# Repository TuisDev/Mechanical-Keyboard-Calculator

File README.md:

# Mechanical-Keyboard-Calculator
A scientific calculator that has mechanical keys

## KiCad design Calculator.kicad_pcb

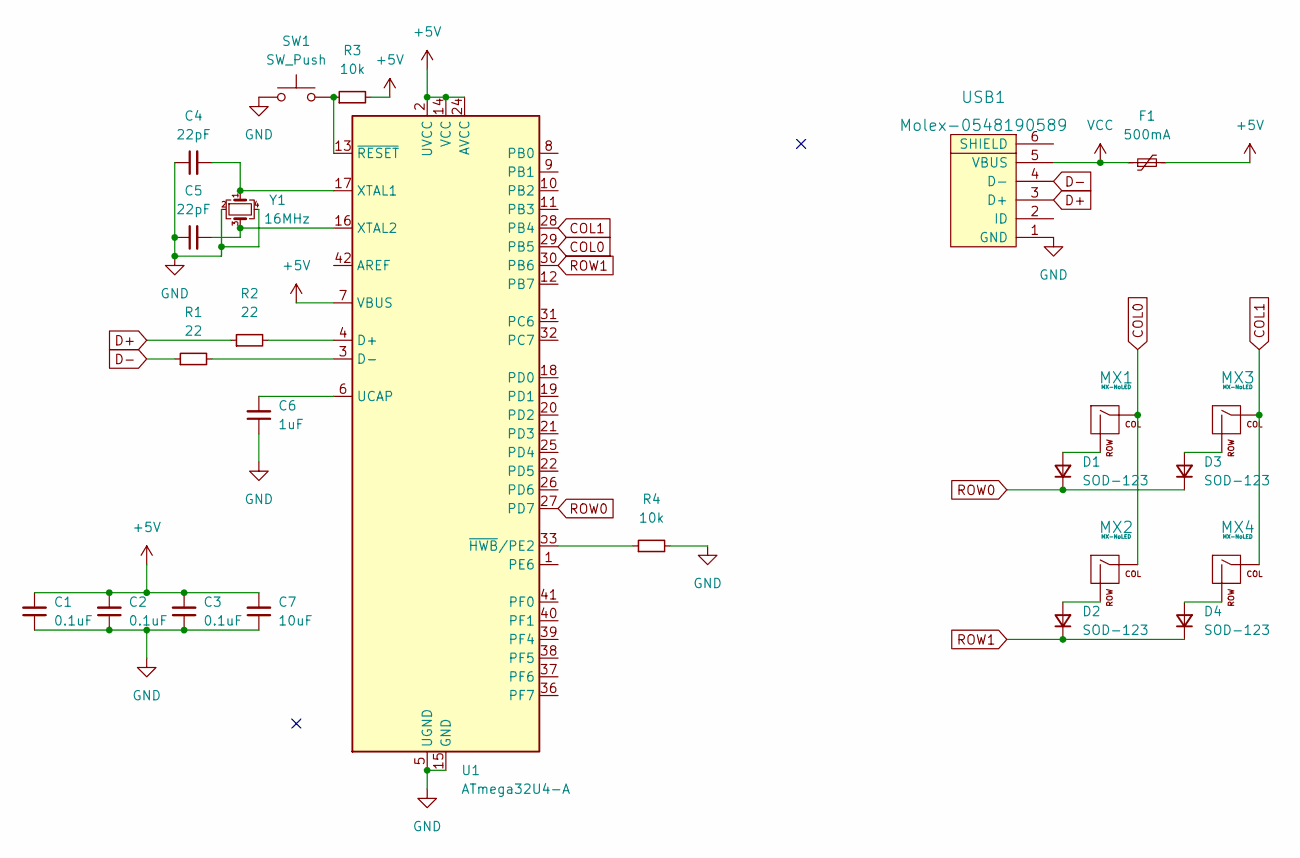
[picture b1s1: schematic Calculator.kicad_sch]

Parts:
C1, C2, C3: 0.1uF; C_0805_2012Metric
C4, C5: 22pF; C_0805_2012Metric
C6: 1uF; C_0805_2012Metric
C7: 10uF; C_0805_2012Metric
D1, D2, D3, D4: SOD-123; D_SOD-123
F1: 500mA; Fuse_1206_3216Metric
MX1, MX2, MX3, MX4: MX-NoLED; MX-1U-NoLED
R1, R2: 22; R_0805_2012Metric
R3, R4: 10k; R_0805_2012Metric
SW1: SW_Push; SKQG-1155865
U1: ATmega32U4-A; TQFP-44_10x10mm_P0.8mm
USB1: Molex-0548190589
Y1: 16MHz; Crystal_SMD_3225-4Pin_3.2x2.5mm

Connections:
+5V: C1.2, C2.2, C3.2, C7.2, F1.2, R3.2, U1.2 (UVCC), U1.7 (VBUS), U1.14 (VCC), U1.24 (AVCC), U1.34 (VCC), U1.44 (AVCC)
COL0: MX1.1 (COL), MX2.1 (COL), U1.29 (PB5)
COL1: MX3.1 (COL), MX4.1 (COL), U1.28 (PB4)
D+: R2.1, USB1.3 (D+)
D-: R1.1, USB1.4 (D-)
GND: C1.1, C2.1, C3.1, C4.1, C5.1, C6.1, C7.1, R4.2, SW1.1, U1.5 (UGND), U1.15 (GND), U1.23 (GND), U1.35 (GND), U1.43 (GND), USB1.1 (GND), Y1.2, Y1.4
unnamed: C4.2, U1.17 (XTAL1), Y1.1
unnamed: C5.2, U1.16 (XTAL2), Y1.3
unnamed: C6.2, U1.6 (UCAP)
unnamed: D1.2 (A), MX1.2 (ROW)
unnamed: D2.2 (A), MX2.2 (ROW)
unnamed: D3.2 (A), MX3.2 (ROW)
unnamed: D4.2 (A), MX4.2 (ROW)
unnamed: R1.2, U1.3 (D-)
unnamed: R2.2, U1.4 (D+)
unnamed: R3.1, SW1.2, U1.13 (~RESET)
unnamed: R4.1, U1.33 (~HWB/PE2)
ROW0: D1.1 (K), D3.1 (K), U1.27 (PD7)
ROW1: D2.1 (K), D4.1 (K), U1.30 (PB6)
VCC: F1.1, USB1.5 (VBUS)

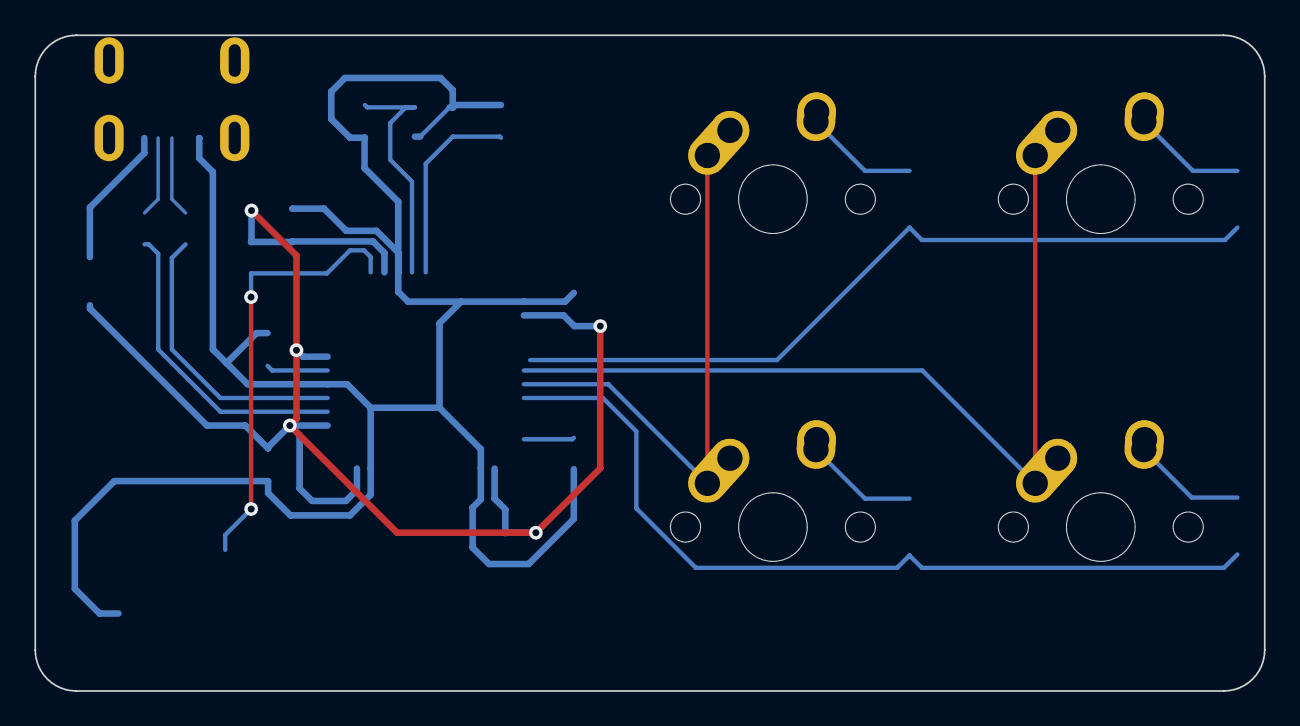
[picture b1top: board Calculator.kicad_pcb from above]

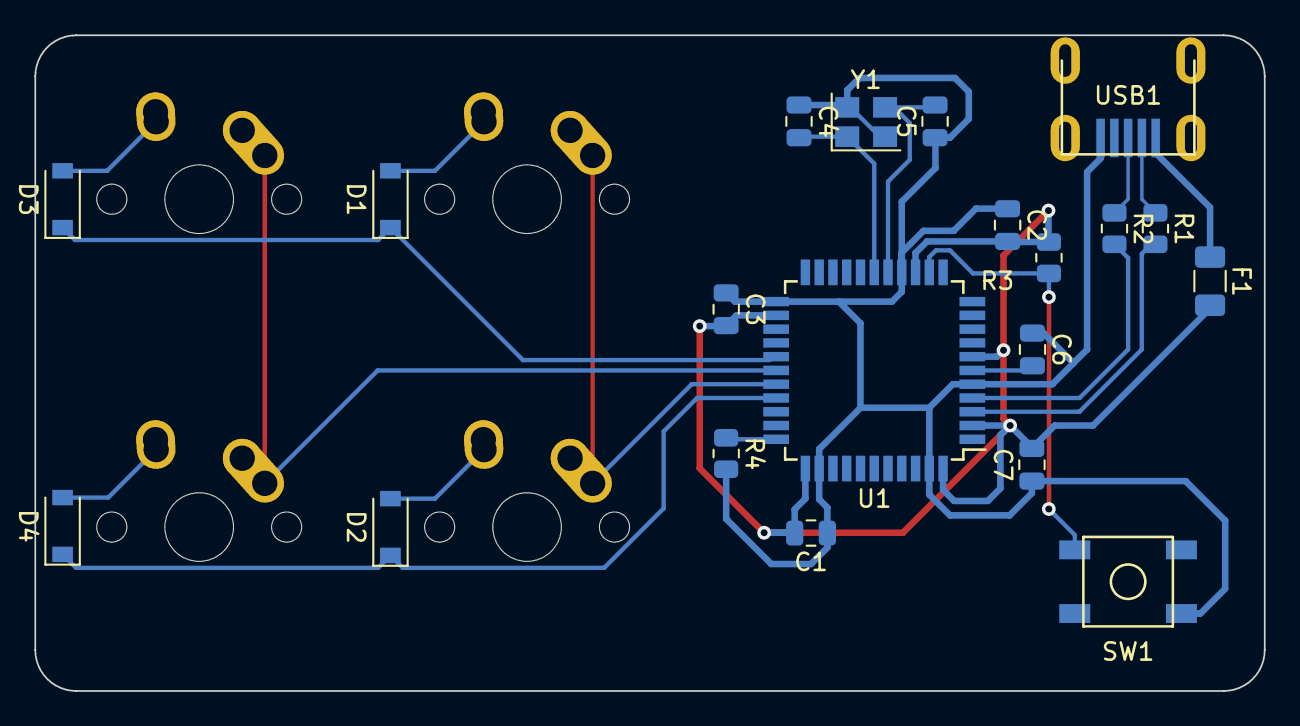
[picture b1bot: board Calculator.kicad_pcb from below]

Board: 2 copper layers, 71.4 x 38.1 mm, 24 parts (20 on the bottom side), 20 nets.

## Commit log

2022-12-05 Added pcb files
2022-12-05 Add submodules
2022-12-06 Add footprint libraries
2022-12-06 Add schematic
2022-12-07 Add PCB
2024-02-05 restarted
2024-02-05 added libraries
2024-02-05 Made schematic
